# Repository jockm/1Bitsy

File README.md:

# 1-Bitsy The SAP CPU

## Files in this Project

- EAGLE Schematic and PCB files
- PDF of the Schematic
- Logisim-Evolution simulation 

## Description 
After reading the book *CPUの創りかた* (translation: *How to Make a CPU*) by Kaoru Watanabe, which describes the creation of a 4 bit CPU called the TD-4. I decided to create a CPU of my own.  I didn't want to spend weeks to months slaving over logism before making a PCB, so I gave myself the goal to make the simplest possible thing that could be called a CPU.  It had to be able to do the following:

- Sequence.  Progress from one instruction to another.
- Selection. Change the course of execution based on some criteria.
- Iteration. Change the course of execution.

There is no ALU at all, no data memory, and no internal registers.  It is just able to give predetermined outputs to some external input.  However the minimum viable system consists of three chips:

- 2 74*161 4-bit counter with clear
- 1 74*02 quad 2 input nor gate

This system allows for addressing 16 bytes of read only 8-bit memory.  Not much (if anything) practical can be done with these constraints, but it does technically meet all the criteria.  As we all know being technically correct is the best kind of correct.

**Personal Note:** I struggled a little to decide the "bitness" of the CPU as that is either based on the ALU width or the data bus width.  The 1Bitsy has no ALU, uses a 8 bit instruction word, 4-bit output, and has only a single bit input.  So it could be seen as a 0, 1, 4, or 8 bit system.  One bit just felt the most intellectually honest

### Expandability 

It would be fairly easy to expand the system to be able to address 256 bytes of 12-bit read only memory by adding addition 74*161s and tweaking the decoding logic.  This is left as an intellectual exercise for the reader

Additionally there is currently an unused bit in the instruction nibble which could be used to add additional instructions.  For example if Bit 5 of the Instruction byte were named `I` and tied to the `ENT` and `ENP` pins of the output register, then every instruction would have a variant that would increment the output register's value:

| `76543210` | `ASM` | Description                               |
| ---------- | ----- | -----------------------------             |     
| `**10VVVV` | `OUT` | Output `VVVV`                             | 
| `**00VVVV` | `OTI` | Increment & Output `VVVV`                 | 
| `0011****` | `NOP` | No Operation                              | 
| `0001****` | `INC` | Increment Output                          | 
| `0101VVVV` | `JMP` | Increment & `PC <- VVVV` If Input Bit Set | 
| `0111VVVV` | `JMP` | `PC <- VVVV` If Input Bit Set             | 
| `1*01VVVV` | `JST` | `PC <- VVVV`                              | 
| `1*11VVVV` | `JST` | Increment &`PC <- VVVV`                   | 

## The System

### I/O

Output consists of 4 output bits (`Out0`...`Out3`), there is a single input bit (`In`).

### Instruction Byte

| Bit(s)   | Name   | Description |
| -------- | -----  | ----------- |
| Bit  7   | `P`    | PC Load     |
| Bit  6   | `C`    | Condition   |
| Bit  5   |        | Unused      |
| Bit  4   | `O`    | Output      |
| Bits 3-0 | `VVVV` | Value       |

### Instructions

| `76543210` | `ASM` | Description                   |
| ---------- | ----- | ----------------------------- |     
| `***0VVVV` | `OUT` | Output `VVVV`                 | 
| `00*1****` | `NOP` | No Operation                  | 
| `01*1VVVV` | `JMP` | `PC <- VVVV` If Input Bit Set | 
| `1**1VVVV` | `JST` | `PC <- VVVV`                  | 

There are two additional "phantom instructions" of dubious utility:

- `01*0VVVV` - `JMO`: Output `VVVV` and Jump to `VVVV`
- `1**0VVVV` - `JSO`: Output `VVVV` and Jump to `VVVV` If Input Bit Set

## Theory of Operation

One of the 74*161s is used as a settable register, and isn't allowed to increment the value. So if the O Bit is not set, the contents of `VVVV` are loaded into the register, and and the `QA`-`QD` pins preserve the output until another `OUT` (or `JMO` or `JSO`) instruction occurs

Instruction Decoding works as follows

- If `O` is 0 then load `VVVV` into the output, regardless of any other bits 
- If `P` is 0 and `C` is 1 then set the `PC` to `VVVV` If In is 1
- If `P` is 1 then set the `PC` to `VVVV`

Or to put it another way:

- `O` is always acted on
- `P` ignores C
- `C` checks if In is set

## License

BSD 2-Clause License

Copyright (c) 2017, Jock Murphy

Redistribution and use in source and binary forms, with or without modification, are permitted provided that the following conditions are met:

1. Redistributions of source code must retain the above copyright notice, this list of conditions and the following disclaimer.

1. Redistributions in binary form must reproduce the above copyright notice, this list of conditions and the following disclaimer in the documentation and/or other materials provided with the distribution.

THIS SOFTWARE IS PROVIDED BY THE COPYRIGHT HOLDERS AND CONTRIBUTORS "AS IS" AND ANY EXPRESS OR IMPLIED WARRANTIES, INCLUDING, BUT NOT LIMITED TO, THE IMPLIED WARRANTIES OF MERCHANTABILITY AND FITNESS FOR A PARTICULAR PURPOSE ARE DISCLAIMED. IN NO EVENT SHALL THE COPYRIGHT HOLDER OR CONTRIBUTORS BE LIABLE FOR ANY DIRECT, INDIRECT, INCIDENTAL, SPECIAL, EXEMPLARY, OR CONSEQUENTIAL DAMAGES (INCLUDING, BUT NOT LIMITED TO, PROCUREMENT OF SUBSTITUTE GOODS OR SERVICES; LOSS OF USE, DATA, OR PROFITS; OR BUSINESS INTERRUPTION) HOWEVER CAUSED AND ON ANY THEORY OF LIABILITY, WHETHER IN CONTRACT, STRICT LIABILITY, OR TORT (INCLUDING NEGLIGENCE OR OTHERWISE) ARISING IN ANY WAY OUT OF THE USE OF THIS SOFTWARE, EVEN IF ADVISED OF THE POSSIBILITY OF SUCH DAMAGE.

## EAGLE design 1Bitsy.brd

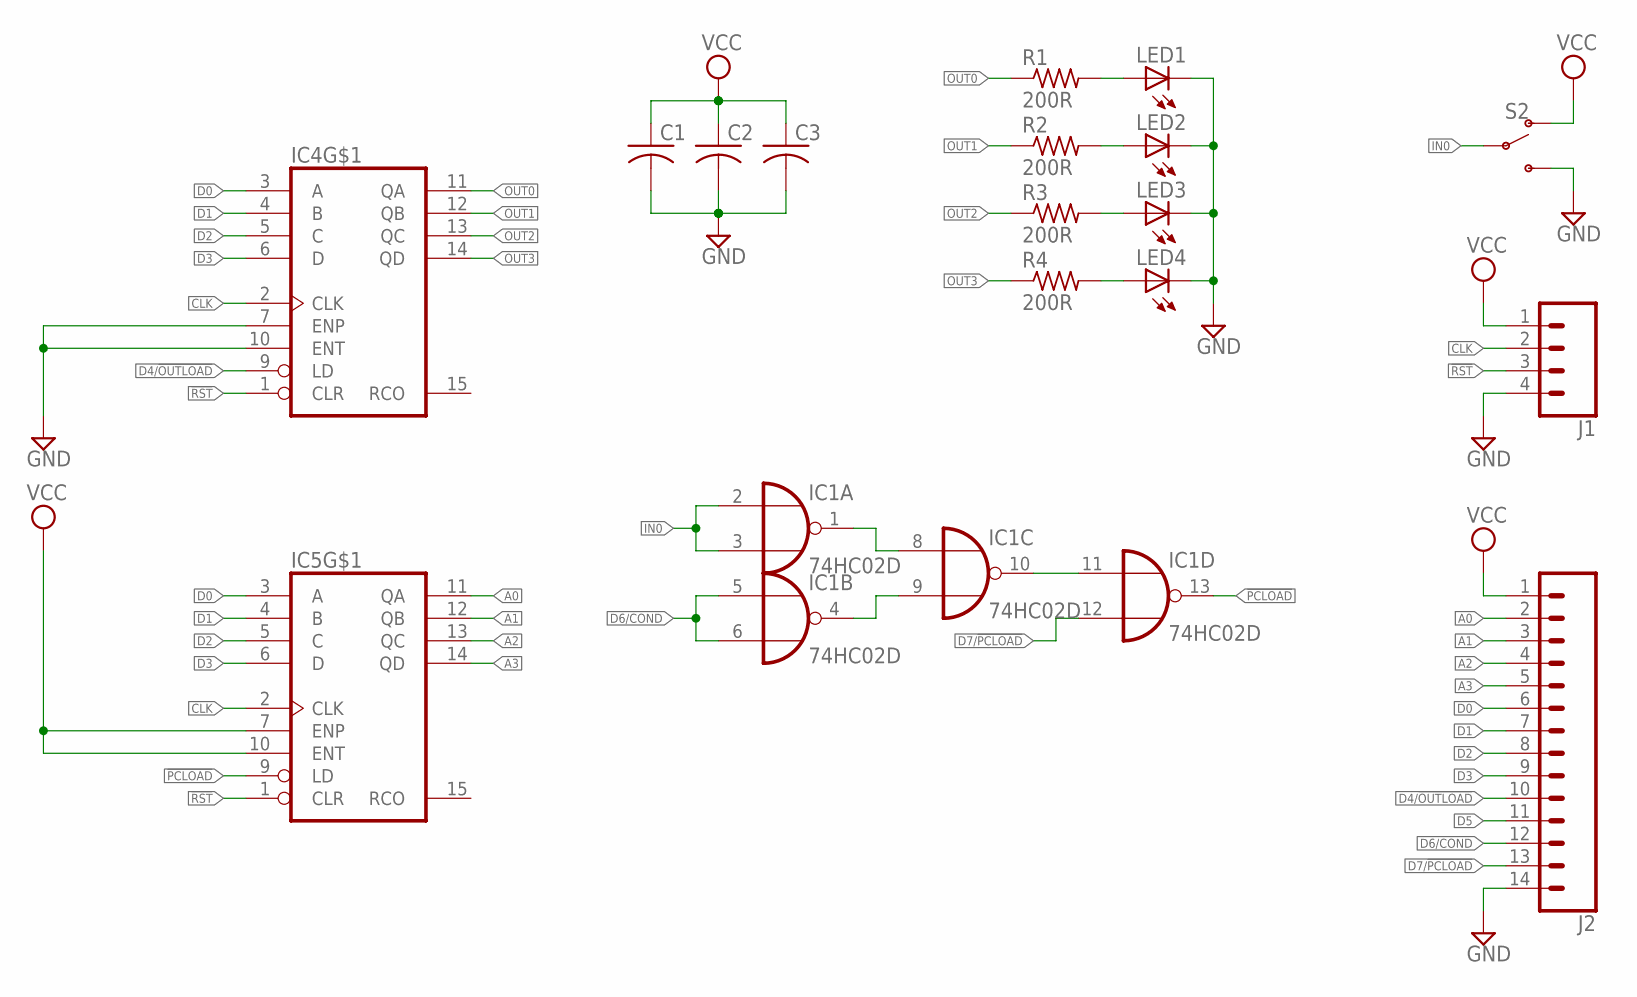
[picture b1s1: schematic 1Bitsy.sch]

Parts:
C1, C2, C3: C-USC0805; C0805
IC1: 74HC02D; SO14
IC4, IC5: 74HC161; SO16
J1: CONN_04; 1X04
J2: CONN_14; 1X14
LED1, LED2, LED3, LED4: LEDCHIP-LED0805; CHIP-LED0805
R1, R2, R3, R4: 200R; R0805
S2: SWITCH-SPDT-SMD-RIGHT-ANGLE; SWITCH_SPST_SMD_A

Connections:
!PCLOAD: IC1.13 (O), IC5.9 (LD)
!RST: IC4.1 (CLR), IC5.1 (CLR), J1.3
A0: IC5.11 (QA), J2.2
A1: IC5.12 (QB), J2.3
A2: IC5.13 (QC), J2.4
A3: IC5.14 (QD), J2.5
CLK: IC4.2 (CLK), IC5.2 (CLK), J1.2
D0: IC4.3 (A), IC5.3 (A), J2.6
D1: IC4.4 (B), IC5.4 (B), J2.7
D2: IC4.5 (C), IC5.5 (C), J2.8
D3: IC4.6 (D), IC5.6 (D), J2.9
D4/!OUTLOAD: IC4.9 (LD), J2.10
D5: J2.11
D6/COND: IC1.5 (I0), IC1.6 (I1), J2.12
D7/!PCLOAD: IC1.12 (I1), J2.13
GND: C1.2, C2.2, C3.2, IC1.7 (GND), IC4.7 (ENP), IC4.8 (GND), IC4.10 (ENT), IC5.8 (GND), J1.4, J2.14, LED1.C, LED2.C, LED3.C, LED4.C, S2.3 (S)
IN0: IC1.2 (I0), IC1.3 (I1), S2.2
unnamed: LED4.A, R4.2
unnamed: LED3.A, R3.2
unnamed: LED2.A, R2.2
unnamed: LED1.A, R1.2
unnamed: IC1.10 (O), IC1.11 (I0)
unnamed: IC1.1 (O), IC1.8 (I0)
unnamed: IC1.4 (O), IC1.9 (I1)
OUT0: IC4.11 (QA), R1.1
OUT1: IC4.12 (QB), R2.1
OUT2: IC4.13 (QC), R3.1
OUT3: IC4.14 (QD), R4.1
VCC: C1.1, C2.1, C3.1, IC1.14 (VCC), IC4.16 (VCC), IC5.7 (ENP), IC5.10 (ENT), IC5.16 (VCC), J1.1, J2.1, S2.1 (O)

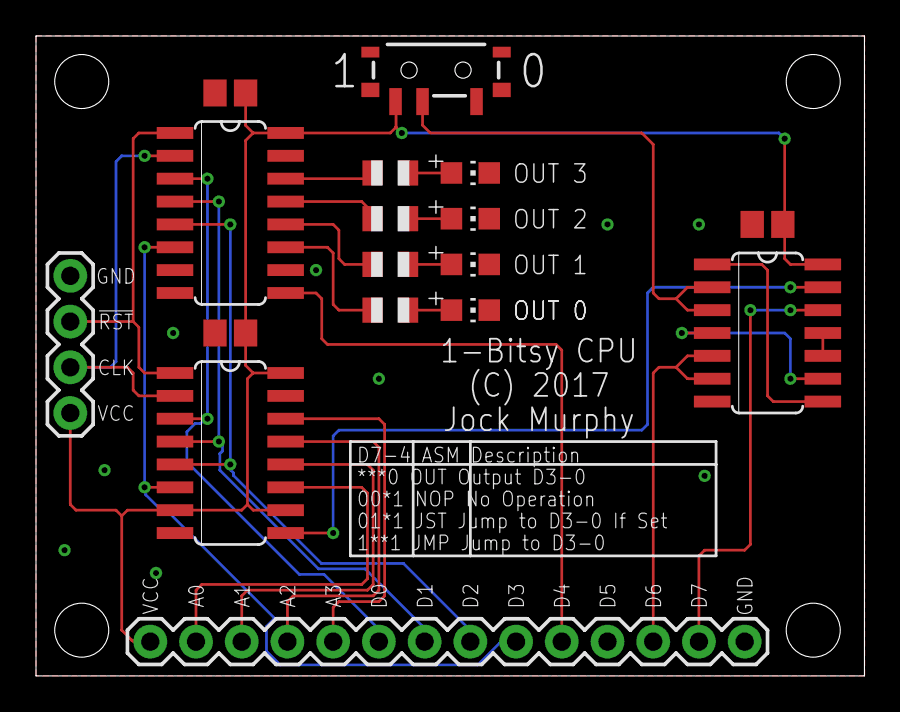
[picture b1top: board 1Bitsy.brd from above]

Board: 2 copper layers, 46.0 x 35.5 mm, 17 parts (0 on the bottom side), 28 nets.

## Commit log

2022-12-28 Update README.md
    Restored lost text
2022-12-28 improved formatting
2022-12-28 Added Schematic PDF
2022-12-28 Added files included, and note on bitness
2022-12-28 updated schematic to document purpose of each section
2022-12-28 removed hidden file
2022-12-28 added gitignore
2022-12-28 added license to readme
2022-12-28 improved formatting added note on expandability
2022-12-28 removed footer from schematic
2022-12-28 created subdirectories
2022-12-28 Added to expandability section
2022-12-28 endless tweaking of the readme

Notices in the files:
parts and their libraries:
SparkFun-Connectors: Licensing: Creative Commons ShareAlike 4.0 International - https://creativecommons.org/licenses/by-sa/4.0
